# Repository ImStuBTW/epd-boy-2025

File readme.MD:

# EPD Boy (2025)

A work in progress ePaper laynard charm.

## Preview

## References

Good Display: https://www.good-display.com/product/388.html

E-Ink Adapter: https://hackaday.io/project/164772-e-ink-adapter

Universal ePaper Display: https://www.pcbway.com/project/shareproject/Universal_E_Paper_adapter_PCB_9b9a845c.html

ZMK Design Guide (BMS Circuit Protection): https://github.com/ebastler/zmk-designguide?tab=readme-ov-file#additional-battery-management-considerations

BMS Footprints: https://github.com/ebastler/marbastlib

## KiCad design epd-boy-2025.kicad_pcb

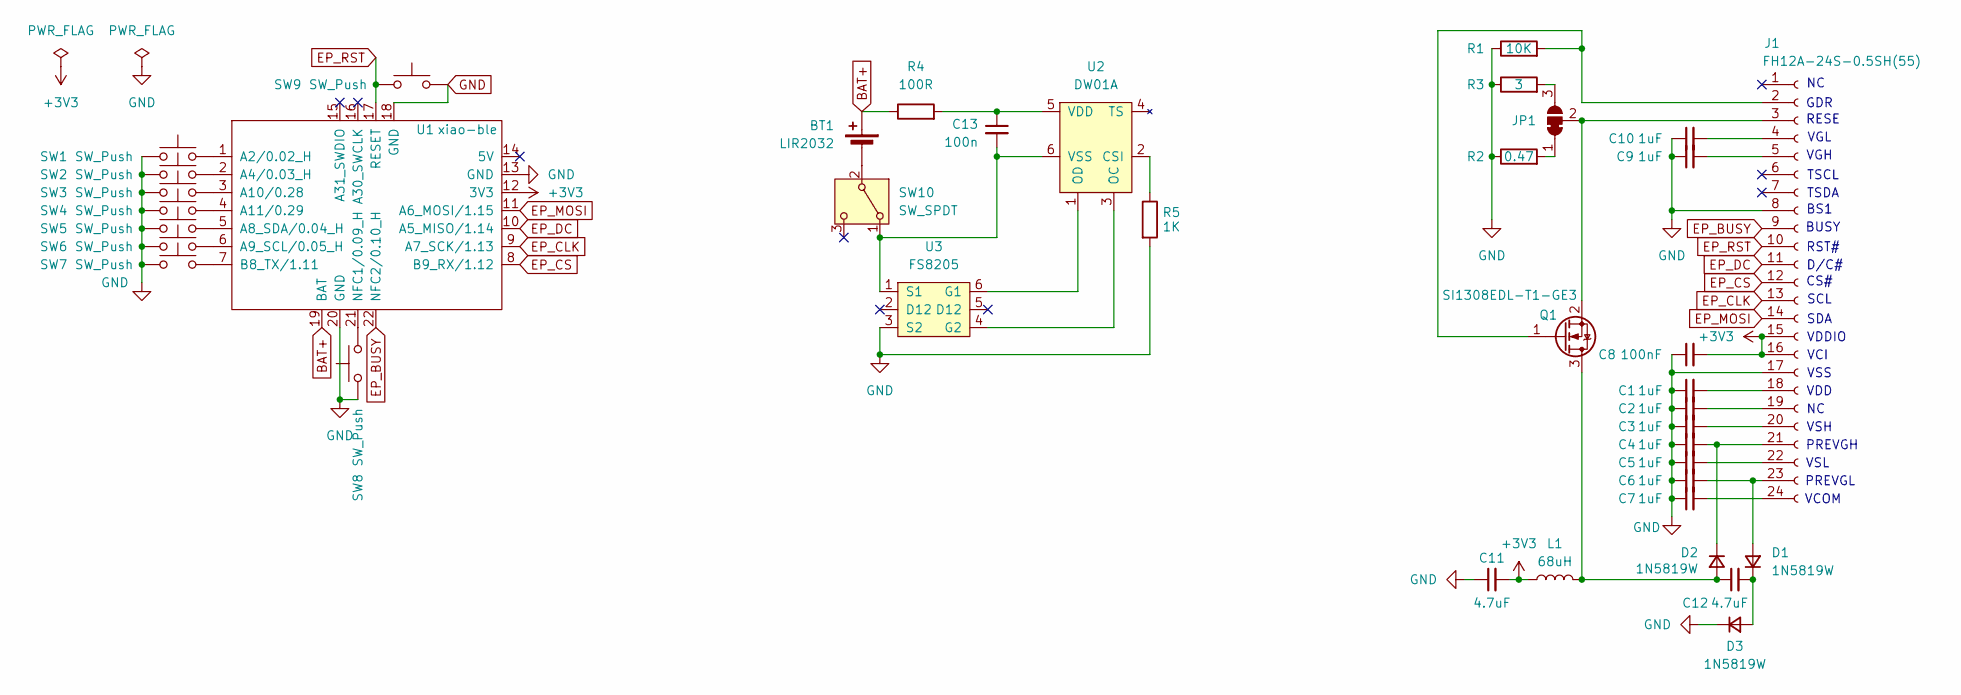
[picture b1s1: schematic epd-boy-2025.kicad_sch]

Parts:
BT1: LIR2032; BatteryHolder_MPD_BC2003_1x2032
C1, C2, C3, C4, C5, C6, C7, C9, C10: 1uF; C_0805_2012Metric_Pad1.18x1.45mm_HandSolder
C8: 100nF; C_0805_2012Metric_Pad1.18x1.45mm_HandSolder
C11, C12: 4.7uF; C_0805_2012Metric_Pad1.18x1.45mm_HandSolder
C13: 100n; C_0805_2012Metric_Pad1.18x1.45mm_HandSolder
D1, D2, D3: 1N5819W; D_SOD-123F
J1: FH12A-24S-0.5SH(55); Hirose_FH12-24S-0.5SH_1x24-1MP_P0.50mm_Horizontal
JP1: SolderJumper_3_Bridged12; SolderJumper-3_P1.3mm_Bridged12_Pad1.0x1.5mm
L1: 68uH; L_1210_3225Metric_Pad1.42x2.65mm_HandSolder
Q1: SI1308EDL-T1-GE3; SOT-23
R1: 10K; R_0805_2012Metric_Pad1.20x1.40mm_HandSolder
R2: 0.47; R_0805_2012Metric_Pad1.20x1.40mm_HandSolder
R3: 3; R_0805_2012Metric_Pad1.20x1.40mm_HandSolder
R4: 100R; R_0805_2012Metric_Pad1.20x1.40mm_HandSolder
R5: 1K; R_0805_2012Metric_Pad1.20x1.40mm_HandSolder
SW1, SW2, SW3, SW4, SW5, SW6, SW7, SW8: SW_Push; SW_Push_SPST_NO_Alps_SKRK
SW9: SW_Push; SW_SPST_CK_KMS2xxGP
SW10: SW_SPDT; SW_SPDT_PCM12
U1: xiao-ble; xiao-ble-smd-cutout-nfc
U2: DW01A; SOT-23-6_Handsoldering; LCSC C61503
U3: FS8205; SOT-23-6_Handsoldering; LCSC C32254

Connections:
+3V3: C8.2, C11.2, J1.15, J1.16, L1.1, U1.12 (3V3)
BAT+: BT1.1 (+), R4.1, U1.19 (BAT)
EP_BUSY: J1.9, U1.22 (NFC2/0.10_H)
EP_CLK: J1.13, U1.9 (A7_SCK/1.13)
EP_CS: J1.12, U1.8 (B9_RX/1.12)
EP_DC: J1.11, U1.10 (A5_MISO/1.14)
EP_MOSI: J1.14, U1.11 (A6_MOSI/1.15)
EP_RST: J1.10, SW9.1, U1.17 (RESET)
GND: C1.1, C2.1, C3.1, C4.1, C5.1, C6.1, C7.1, C8.1, C9.1, C10.1, C11.1, D3.1 (K), J1.8, J1.17, R1.1, R2.1, R3.1, R5.2, SW1.1, SW2.1, SW3.1, SW4.1, SW5.1, SW6.1, SW7.1, SW8.1, SW9.2, U1.13 (GND), U1.18 (GND), U1.20 (GND), U3.3 (S2)
unnamed: BT1.2 (-), SW10.2 (B)
unnamed: C6.2, D1.2 (A), J1.23
unnamed: C12.2, D1.1 (K), D3.2 (A)
unnamed: C12.1, D2.2 (A), L1.2, Q1.3 (D)
unnamed: C4.2, D2.1 (K), J1.21
unnamed: J1.2, Q1.1 (G), R1.2
unnamed: J1.3, JP1.2 (C), Q1.2 (S)
unnamed: C10.2, J1.4
unnamed: C9.2, J1.5
unnamed: C1.2, J1.18
unnamed: C2.2, J1.19
unnamed: C3.2, J1.20
unnamed: C5.2, J1.22
unnamed: C7.2, J1.24
unnamed: JP1.1 (A), R2.2
unnamed: JP1.3 (B), R3.2
unnamed: C13.2, SW10.1 (A), U2.6 (VSS), U3.1 (S1)
unnamed: SW1.2, U1.1 (A2/0.02_H)
unnamed: SW2.2, U1.2 (A4/0.03_H)
unnamed: SW5.2, U1.5 (A8_SDA/0.04_H)
unnamed: SW6.2, U1.6 (A9_SCL/0.05_H)
unnamed: SW3.2, U1.3 (A10/0.28)
unnamed: SW4.2, U1.4 (A11/0.29)
unnamed: SW7.2, U1.7 (B8_TX/1.11)
unnamed: SW8.2, U1.21 (NFC1/0.09_H)
unnamed: R5.1, U2.2 (CSI)
unnamed: U2.3 (OC), U3.4 (G2)
unnamed: U2.1 (OD), U3.6 (G1)
unnamed: C13.1, R4.2, U2.5 (VDD)

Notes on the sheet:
BS1
VCI
VSS
SCL
VCOM
VSL
BUSY
PREVGL
TSDA
D/C#
SDA
VDDIO
RST#
VGL
GDR
CS#
TSCL
PREVGH
VSH
RESE
VDD
VGH

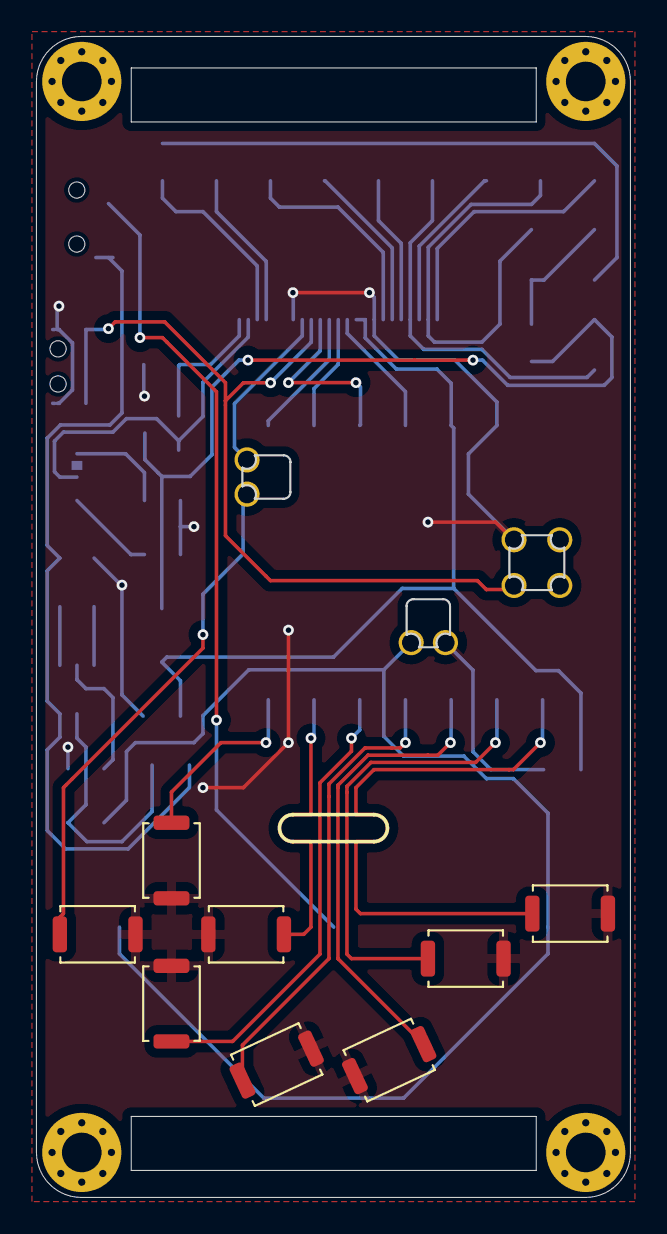
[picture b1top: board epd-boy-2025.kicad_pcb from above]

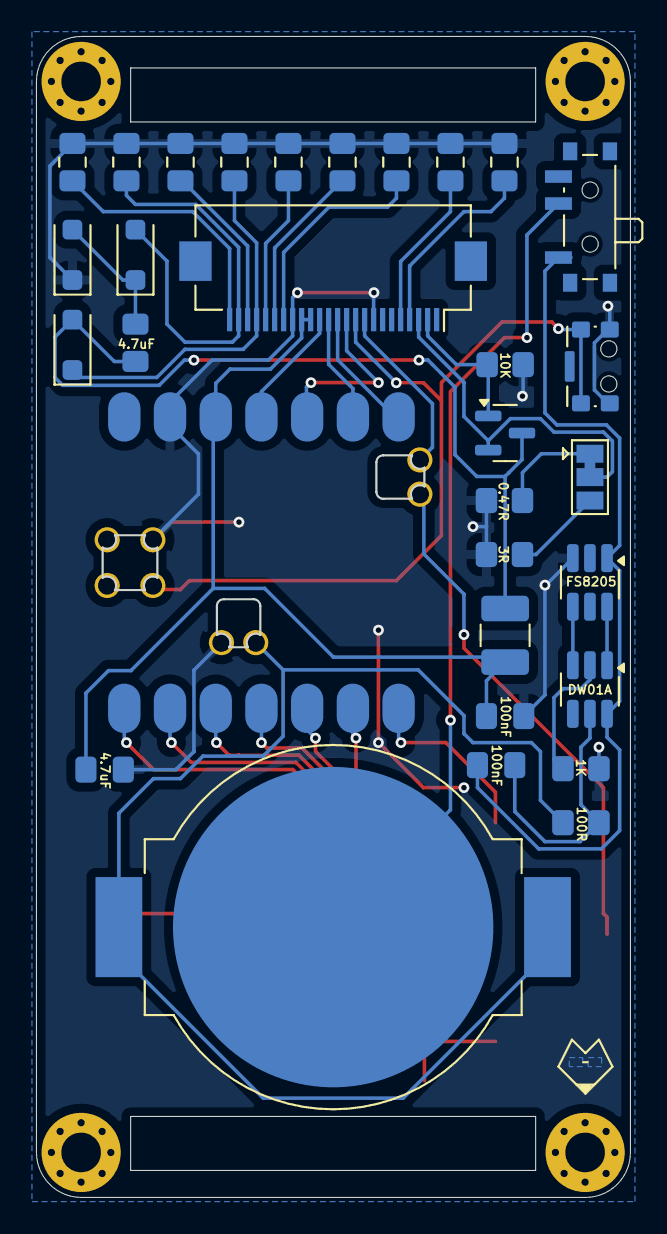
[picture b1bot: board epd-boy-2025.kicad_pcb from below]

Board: 2 copper layers, 32.9 x 64.4 mm, 39 parts (31 on the bottom side), 38 nets.

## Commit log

2025-05-08 Revision
2025-05-09 Rerouted
